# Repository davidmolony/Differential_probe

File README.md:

# Differential_probe
Differential probe, 4 channel for motor control (e.g. IGBT inverters). This is an alternative to using expensive and unobtainable isolation amplifiers.

Be careful. High voltage is dangerous, You are on your own. You take responsibility for yourself and any consequences entirely.

Untested 18/01/2023, on order. 

If you are planning on attaching this to high voltage, 
use UL rated 3kV resistors e.g. Bourns CHV2512-FX-1004ELF and ensure you do not breach the resistor pseudo isolation barrier.
Ground the low voltage side if possible. DO NOT put only capacitors to ground, as this could result in the 1Mohm charging them to mid rail voltage.

The ones specified for JLCPCB are not safety rated, they are for prototyping or non safety or low voltage application.

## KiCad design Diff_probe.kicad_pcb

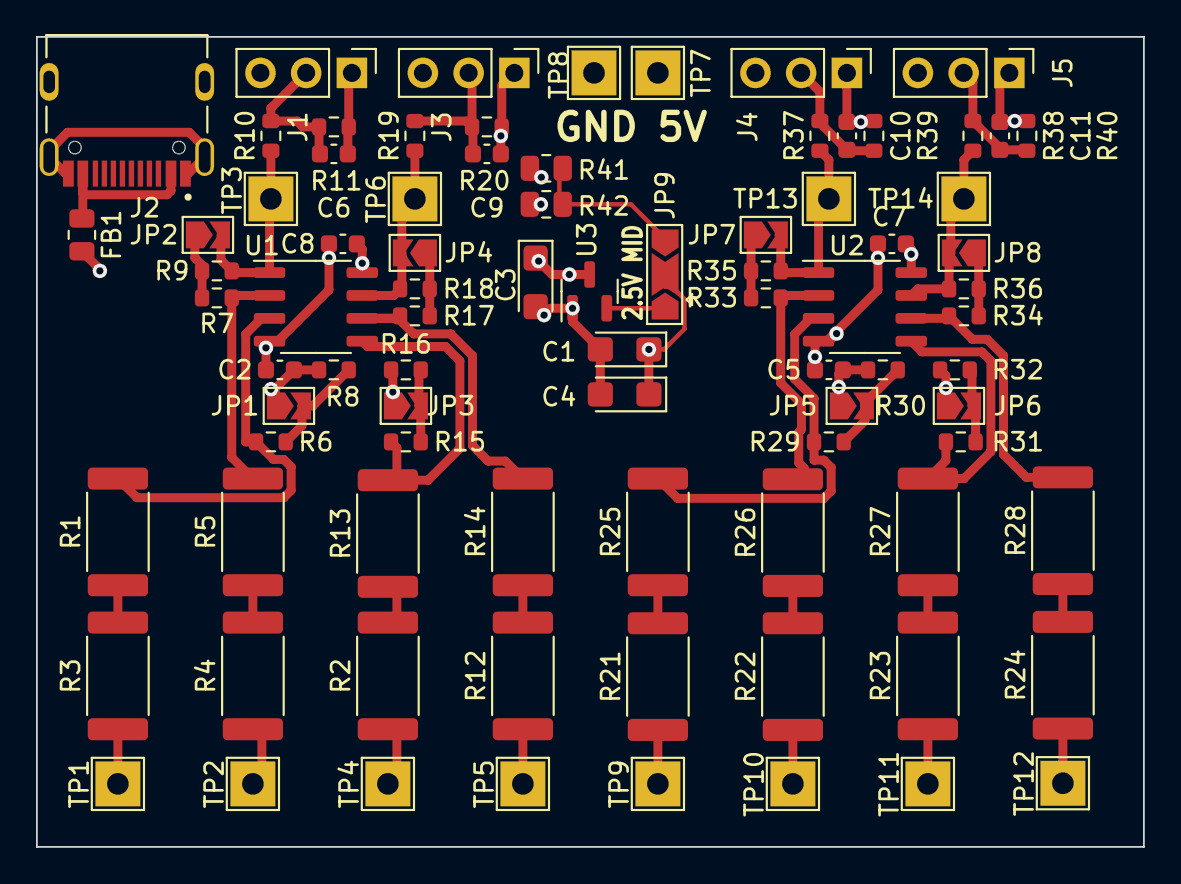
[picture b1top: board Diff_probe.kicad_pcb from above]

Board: 4 copper layers, 61.5 x 45.0 mm, 85 parts (0 on the bottom side), 46 nets.

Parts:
C1, C3, C4: C_10uF_Tant; CP_EIA-3216-18_Kemet-A
C2, C5, C7, C8: C_100nF; C_0603_1608Metric
C6, C9, C10, C11: C_47pF; C_0603_1608Metric
FB1: FerriteBead_Small; R_0805_2012Metric
J1, J3, J4, J5: Conn_01x03_Male; PinHeader_1x03_P2.54mm_Vertical
J2: TYPE-C-31-M-12; HRO_TYPE-C-31-M-12
JP1, JP2, JP3, JP4, JP5, JP6, JP7, JP8: Jumper_2_Open; SolderJumper-2_P1.3mm_Open_TrianglePad1.0x1.5mm
JP9: Jumper_3_Open; SolderJumper-3_P2.0mm_Open_TrianglePad1.0x1.5mm
R1, R2, R3, R4, R5, R12, R13, R14, R21, R22, R23, R24, R25, R26, R27, R28: R_1Mohm; R_2512_6332Metric
R6, R7, R15, R17, R29, R31, R33, R34: R_10k; R_0603_1608Metric
R8, R9, R16, R18, R30, R32, R35, R36: R_40k; R_0603_1608Metric
R10, R19, R37, R38: R_47; R_0603_1608Metric
R11, R20, R39, R40: R_DNP; R_0603_1608Metric
R41, R42: R_100; R_0805_2012Metric
TP1, TP2, TP3, TP4, TP5, TP6, TP7, TP8, TP9, TP10, TP11, TP12, TP13, TP14: TestPoint; TestPoint_THTPad_2.5x2.5mm_Drill1.2mm
U1, U2: OPA2356xxD; SO-8_3.9x4.9mm_P1.27mm
U3: XC6206PxxxMR; SOT-23

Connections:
+2V5: C1.1, C2.1, C4.1, C5.1, JP1.1 (A), JP3.1 (A), JP5.1 (A), JP6.1 (A), JP9.2 (C), R8.1, R16.1, R30.1, R32.1
+5V: C3.1, C7.1, C8.1, FB1.2, J1.3, J3.3, J4.3, J5.3, R41.1, TP7.1, U1.8 (V+), U2.8 (V+), U3.3 (VI)
GND: C1.2, C2.2, C3.2, C4.2, C5.2, C6.1, C7.2, C8.2, C9.1, C10.1, C11.1, J1.1, J2.A1B12 (GND), J2.B1A12 (GND), J2.S1 (SHIELD), J2.S2 (SHIELD), J2.S3 (SHIELD), J2.S4 (SHIELD), J3.1, J4.1, J5.1, R11.2, R20.2, R39.2, R40.2, R42.2, TP8.1, U1.4 (V-), U2.4 (V-), U3.1 (GND)
unnamed: FB1.1, J2.A4B9 (VBUS), J2.B4A9 (VBUS)
unnamed: JP1.2 (B), R6.2, R8.2
unnamed: JP2.1 (A), R7.2, R9.1
unnamed: JP2.2 (B), R9.2, R10.1, TP3.1, U1.1
unnamed: JP3.2 (B), R15.2, R16.2
unnamed: JP4.1 (A), R17.2, R18.1
unnamed: JP4.2 (B), R18.2, R19.1, TP6.1, U1.7
unnamed: JP5.2 (B), R29.2, R30.2
unnamed: JP6.2 (B), R31.2, R32.2
unnamed: JP7.1 (A), R33.2, R35.1
unnamed: JP7.2 (B), R35.2, R37.1, TP13.1, U2.1
unnamed: JP8.1 (A), R34.2, R36.1
unnamed: JP8.2 (B), R36.2, R38.1, TP14.1, U2.7
unnamed: R1.1, R3.2
unnamed: R1.2, R6.1, U1.3 (+)
unnamed: R2.1, TP4.1
unnamed: R3.1, TP1.1
unnamed: R4.1, TP2.1
unnamed: R4.2, R5.1
unnamed: R5.2, R7.1, U1.2 (-)
unnamed: R12.1, TP5.1
unnamed: R12.2, R14.1
unnamed: R2.2, R13.1
unnamed: R13.2, R15.1, U1.5 (+)
unnamed: R14.2, R17.1, U1.6 (-)
unnamed: R21.1, TP9.1
unnamed: R21.2, R25.1
unnamed: R22.1, TP10.1
unnamed: R22.2, R26.1
unnamed: R23.1, TP11.1
unnamed: R23.2, R27.1
unnamed: R24.1, TP12.1
unnamed: R24.2, R28.1
unnamed: R25.2, R29.1, U2.3 (+)
unnamed: R26.2, R33.1, U2.2 (-)
unnamed: R27.2, R31.1, U2.5 (+)
unnamed: R28.2, R34.1, U2.6 (-)
unnamed: JP9.3 (B), R41.2, R42.1
unnamed: JP9.1 (A), U3.2 (VO)
Output1: C6.2, J1.2, R10.2, R11.1
Output2: C9.2, J3.2, R19.2, R20.1
Output3: C10.2, J4.2, R37.2, R39.1
Output4: C11.2, J5.2, R38.2, R40.1

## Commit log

2023-01-18 Initial commit, untested hardware design.
2023-01-21 As ordered prototype 20230121
2023-01-21 Pics of layout and board render
